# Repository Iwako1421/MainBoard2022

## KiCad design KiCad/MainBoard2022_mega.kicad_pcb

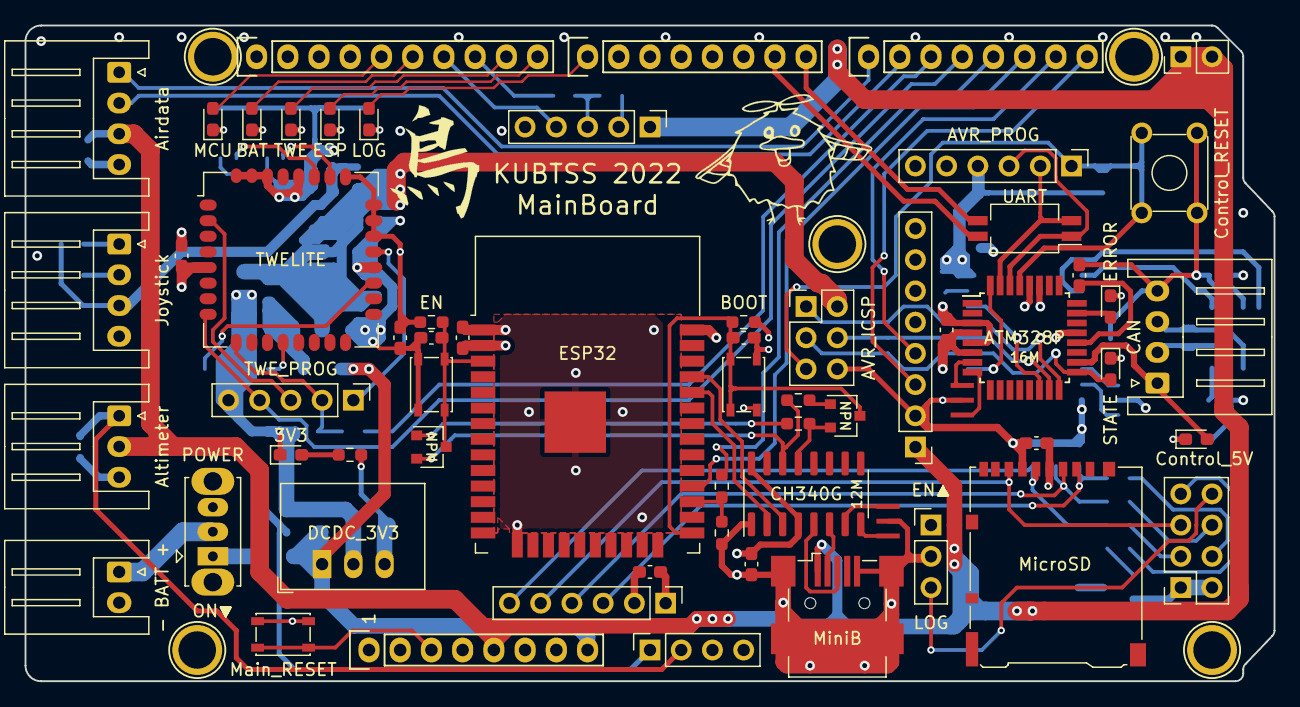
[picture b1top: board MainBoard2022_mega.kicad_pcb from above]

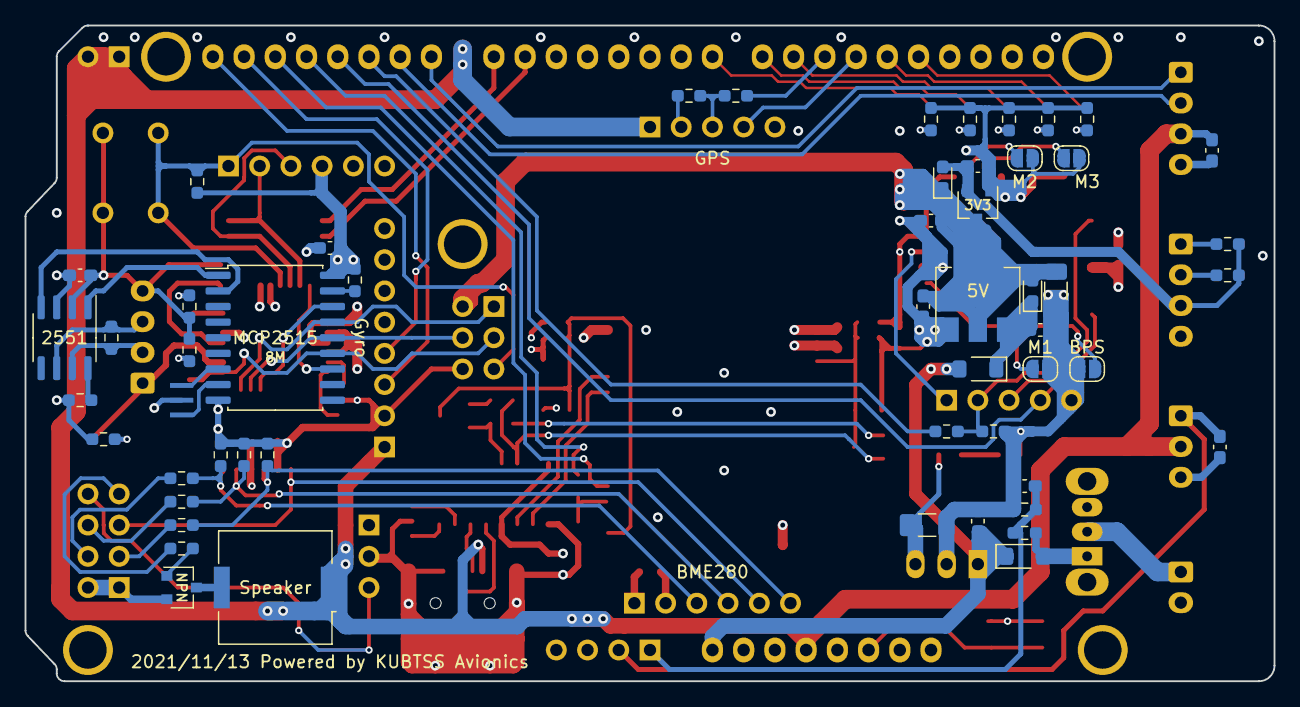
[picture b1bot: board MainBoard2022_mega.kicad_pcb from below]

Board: 4 copper layers, 101.6 x 53.3 mm, 121 parts (54 on the bottom side), 92 nets.

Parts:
8M: 8MHz; Resonator_SMD_muRata_CSTxExxV-3Pin_3.0x1.1mm
12M: 12MHz; Resonator_SMD_muRata_CSTxExxV-3Pin_3.0x1.1mm
16M: 16MHz; Resonator_SMD_muRata_CSTxExxV-3Pin_3.0x1.1mm
C1, C2, C3, C4, C6, C9, C10, C12, C16, C17, C18, C19, C20, C21, C22: 0.1u; C_0603_1608Metric_Pad1.08x0.95mm_HandSolder
C5, C8, C11: 10u; C_0603_1608Metric_Pad1.08x0.95mm_HandSolder
C7, C13: 100u; C_1206_3216Metric_Pad1.33x1.80mm_HandSolder
C14, C15: 2.2u; C_0603_1608Metric_Pad1.08x0.95mm_HandSolder
D1: 3V3; LED_0603_1608Metric_Pad1.05x0.95mm_HandSolder
D2, D4: RB160M; D_2616Metric_HandSolder
D3: Control_5V; LED_0603_1608Metric_Pad1.05x0.95mm_HandSolder
D5, D9: RB520S; D_0603_1608Metric_Pad1.05x0.95mm_HandSolder
D10: STATE; LED_0603_1608Metric_Pad1.05x0.95mm_HandSolder
D11: ERROR; LED_0603_1608Metric_Pad1.05x0.95mm_HandSolder
D12: MCU; LED_0603_1608Metric_Pad1.05x0.95mm_HandSolder
D13: LOG; LED_0603_1608Metric_Pad1.05x0.95mm_HandSolder
D14: ESP; LED_0603_1608Metric_Pad1.05x0.95mm_HandSolder
D15: TWE; LED_0603_1608Metric_Pad1.05x0.95mm_HandSolder
D16: BAT; LED_0603_1608Metric_Pad1.05x0.95mm_HandSolder
EN▲: LOG; PinHeader_1x03_P2.54mm_Vertical
J1: - BATT +; JST_XH_S2B-XH-A_1x02_P2.50mm_Horizontal
J2: MiniB; USB_Mini-B_Wuerth_65100516121_Horizontal
J3: Joystick; JST_XH_S4B-XH-A_1x04_P2.50mm_Horizontal
J4: AVR_PROG; PinHeader_1x06_P2.54mm_Vertical
J5: CAN; JST_XH_S4B-XH-A_1x04_P2.50mm_Horizontal
J6: AVR_ICSP; PinHeader_2x03_P2.54mm_Vertical
J7: GPS; PinHeader_1x05_P2.54mm_Vertical
J8: TWE_PROG; PinHeader_1x05_P2.54mm_Vertical
J9: Gyro; PinHeader_1x08_P2.54mm_Vertical
J10: Altimeter; JST_XH_S3B-XH-A_1x03_P2.50mm_Horizontal
J11: Airdata; JST_XH_S4B-XH-A_1x04_P2.50mm_Horizontal
J12: MicroSD; microSD_HC_Hirose_DM3AT-SF-PEJM5
J13: BME280; PinHeader_1x06_P2.54mm_Vertical
JP1: M1; SolderJumper-2_P1.3mm_Open_RoundedPad1.0x1.5mm
JP2: M2; SolderJumper-2_P1.3mm_Open_RoundedPad1.0x1.5mm
JP3: M3; SolderJumper-2_P1.3mm_Open_RoundedPad1.0x1.5mm
JP4: BPS; SolderJumper-2_P1.3mm_Open_RoundedPad1.0x1.5mm
LS1: Speaker; Buzzer_Murata_PKMCS0909E4000-R1
ON▼: POWER; SW_Slide_1P2T_CK_OS102011MS2Q
P1: Power; Socket_Strip_Arduino_1x08
P2: Analog; PinSocket_1x04_P2.54mm_Vertical
P5: PWM; Socket_Strip_Arduino_1x10
P6: PWM; Socket_Strip_Arduino_1x08
P7: Communication; Socket_Strip_Arduino_1x08
P8, P10, P11, P12, P13: CONN_01X01; Arduino_1pin
P14: Digital; PinSocket_2x04_P2.54mm_Vertical
P15: 5V; PinSocket_2x01_P2.54mm_Vertical
Q1, Q2, Q3: NPN; SC-59
R1, R2, R3, R4, R5, R6, R7, R11, R16, R27: 10k; R_0603_1608Metric_Pad0.98x0.95mm_HandSolder
R8: 120; R_0603_1608Metric_Pad0.98x0.95mm_HandSolder
R9, R15, R17, R23, R24, R25: 1.5k; R_0603_1608Metric_Pad0.98x0.95mm_HandSolder
R10, R13, R18, R19, R20, R21, R22, R26, R29, R30, R31, R32, R33, R38, R39: 1k; R_0603_1608Metric_Pad0.98x0.95mm_HandSolder
R12, R28: 4.7k; R_0603_1608Metric_Pad0.98x0.95mm_HandSolder
SW2: BOOT; SW_SPST_PTS810
SW3: EN; SW_SPST_PTS810
SW4: UART; SW_DIP_SPSTx02_Slide_Copal_CHS-02B_W7.62mm_P1.27mm
SW5: Control_RESET; SW_TH_Tactile_Omron_B3F-10xx
SW7: Main_RESET; SW_SPST_PTS810
U1: CH340G; SOIC-16_3.9x9.9mm_P1.27mm
U2: DCDC_3V3; Converter_DCDC_RECOM_R-78E-0.5_THT
U3: ESP32; ESP32-WROOM-32
U4: 2551; SOIC-8_3.9x4.9mm_P1.27mm
U5: 5V; SOT-223-3_TabPin2
U6: 3V3; SOT-23W
U7: MCP2515; SOIC-18W_7.5x11.6mm_P1.27mm
U8: TWELITE; MonoWireless_TWE-L-WX
U9: ATmega328P-AU; TQFP-32_7x7mm_P0.8mm

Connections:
+3.3VP: C15.1, D9.2, J3.3, R1.2, R2.1, U6.2
+3V3: C1.2, C6.1, C7.1, C8.2, C9.2, C18.2, C20.1, J12.4, J13.1, R7.1, R11.1, R38.2, U1.4, U1.16, U2.3, U3.2, U8.5, U8.22, U8.23, U8.24, U8.25
+5V: C16.1, J2.1, J7.1, J9.1, J10.2, J11.3, LS1.1, P1.5, P15.1, P15.2
+5VP: C10.2, C12.1, C13.1, C14.1, C17.2, C21.2, D3.2, D5.2, D9.1, J4.4, J5.1, J6.2, R16.1, R27.1, U4.3, U5.2, U6.3, U7.18, U9.4, U9.6, U9.18
AVR_CS: U7.16, U9.14
AVR_INT: U7.12, U9.32
AVR_MISO: J6.1, U7.15, U9.16
AVR_MOSI: J6.4, U7.14, U9.15
AVR_RST: J4.1, J6.5, R27.2, SW5.1, U9.29
AVR_RX: J4.3, SW4.1, U9.30
AVR_SCK: D10.2, J6.3, U7.13, U9.17
AVR_SCL: J3.2, R2.2, U9.28
AVR_SDA: J3.1, R1.1, U9.27
AVR_TX: J4.2, SW4.2, U9.31
Altimeter: C22.2, J10.1, P2.2
BATT_SENS: C4.1, P2.1, R5.2, R6.1
CAN_H: J5.2, R8.1, U4.7
CAN_L: J5.3, R8.2, U4.6
DTR: Q1.2, R4.2, U1.13
EN: C3.2, Q2.3, R7.2, SW3.2, U3.3
ESP_RX0: U1.2, U3.34
ESP_RX2: R9.1, R10.2, U3.27
ESP_TX0: U1.3, U3.35
ESP_TX2: P7.6, U3.28
GND: 8M.2, 12M.2, 16M.2, C1.1, C2.2, C3.1, C4.2, C5.2, C6.2, C7.2, C8.1, C9.1, C10.1, C11.2, C12.2, C13.2, C14.2, C15.2, C16.2, C17.1, C18.1, C19.1, C20.2, C21.1, C22.1, D1.1, EN▲.2, J1.2, J2.5, J2.6, J3.4, J4.6, J5.4, J6.6, J7.2, J8.5, J9.2, J10.3, J11.4, J12.6, J13.2, JP1.1, JP2.1, JP3.1, JP4.1, P1.6, P1.7, P5.4, P14.1, P14.2, Q3.2, R6.2, R9.2, R12.2, R15.2, R17.2, R19.1, R23.2, R24.2, R25.2, R26.1, R29.1, R30.1, R31.1, R32.1, R33.1, R39.1, SW2.2, SW3.1, SW5.2, SW7.2, U1.1, U2.2, U3.1, U3.15, U3.38, U3.39, U4.2, U5.1, U6.1, U7.9, U8.20, U8.28, U8.30, U8.31, U8.32, U9.3, U9.5, U9.21
IO0: C2.1, Q1.3, R11.2, SW2.1, U3.25
LED_BATT_LO: D16.2, P5.6
LED_ERROR: D12.2, P5.5
LED_ESP: D14.2, P5.10
LED_LOG: D13.2, P6.1
LED_TWE: D15.2, P5.9
LOGGER_STANDBY: EN▲.3, P14.8
MEGA_CS: P14.4, R20.2
MEGA_CS_3V3: J12.2, J13.3, R20.1, R25.1
MEGA_MISO: J12.7, J13.5, P14.5
MEGA_MOSI: P14.6, R21.2
MEGA_MOSI_3V3: J12.3, J13.4, R21.1, R24.1
MEGA_RESET: P1.3, SW7.1
MEGA_RX0: P6.8, SW4.3
MEGA_RX2: J8.4, P7.4, U8.8
MEGA_RX3: J11.2, P7.2
MEGA_RX4: J7.4, P5.7
MEGA_SCK: P14.3, R22.2
MEGA_SCK_3V3: J12.5, J13.6, R22.1, R23.1
MEGA_SCL: J9.3, P7.8
MEGA_SDA: J9.4, P7.7
MEGA_TX0: P6.7, SW4.4
MEGA_TX1: P7.5, R10.1
MEGA_TX2: P7.3, R18.1
MEGA_TX3: J11.1, P7.1
MEGA_TX4: P5.8, R13.2
unnamed: C11.1, D4.1, D5.1, U5.3
unnamed: C19.2, U9.20
unnamed: D1.2, R38.1
unnamed: D2.2, ON▼.1, R5.1
unnamed: D3.1, R39.2
unnamed: D10.1, R19.2
unnamed: D11.1, R26.2
unnamed: D11.2, U9.23
unnamed: D12.1, R29.2
unnamed: D13.1, R30.2
unnamed: D14.1, R31.2
unnamed: D15.1, R32.2
unnamed: D16.1, R33.2
unnamed: J1.1, ON▼.2
unnamed: J2.2, U1.6
unnamed: J2.3, U1.5
unnamed: J7.3, R13.1, R15.1
unnamed: JP1.2, U8.12
unnamed: JP2.2, U8.26
unnamed: JP3.2, U8.27
unnamed: JP4.2, U8.19
unnamed: LS1.2, Q3.3
unnamed: Q1.1, R3.1
unnamed: Q2.1, R4.1
unnamed: Q3.1, R28.1
unnamed: R12.1, U4.8
unnamed: R16.2, U7.17
unnamed: 12M.3, U1.7
unnamed: 12M.1, U1.8
unnamed: U4.1, U7.1
unnamed: U4.4, U7.2
unnamed: 8M.3, U7.7
unnamed: 8M.1, U7.8
unnamed: 16M.3, U9.7
unnamed: 16M.1, U9.8
RTS: Q2.2, R3.2, U1.14
Speaker: P14.7, R28.2
TWE_PRG: J8.3, U8.2
TWE_RST: J8.1, U8.21
TWE_RX: J8.2, R17.1, R18.2, U8.9
VCC: C5.1, D2.1, D4.2, P1.8, U2.1
